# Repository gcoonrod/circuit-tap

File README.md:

<!--
 Copyright 2023 Greg Coonrod
 
 Licensed under the Apache License, Version 2.0 (the "License");
 you may not use this file except in compliance with the License.
 You may obtain a copy of the License at
 
     http://www.apache.org/licenses/LICENSE-2.0
 
 Unless required by applicable law or agreed to in writing, software
 distributed under the License is distributed on an "AS IS" BASIS,
 WITHOUT WARRANTIES OR CONDITIONS OF ANY KIND, either express or implied.
 See the License for the specific language governing permissions and
 limitations under the License.
-->

# Circuit Tap

A low-speed digital logic analyzer designed around 74HC165 shift registers and the ATMega4809 MCU.

## Design

The Circuit Tap is designed to serve as a digital logic analyzer for primarily low speed circuits (<= 1Mhz). It is intended to aid in debugging the [RetroStack](https://github.com/gcoonrod/retro-stack), a 6502 based hobbyist computer. As I do not (at the time of designing this tool) own an oscilliscope or logic analyzer, I needed a way to monitor the address bus, data bus, and numerous control signals of the RetroStack while the clock was freely running. For very simple programs it was sufficient to use a manually stepped clock to debug, but the addition of IO peripherals and more complex programs have made it prohibitively time consuming to continue manual clock control.

### Data Capture

The Circuit Tap has 6 low speed 8-bit input ports and one full speed 8-bit port. The low speed ports are implemented with 74HC165 parallel load shift registers which allows for the simultaneous capture of up to 48 signals on a single clock transition. However, those bits must be shifted out before (~10 mcu clock cycles) before another sample can be taken. This is the primary limiting factor for the sampling speed of the low speed inputs. The full speed port is directly mapped to Port D of the 4809 and can be read from or written to as fast as the mcu is capable.

### Goals

- Reliably capture signals at ~1Mhz
- Read test plans from an SD card or UART
- Write test results to SD or UART
- Integrate with desktop GUI (TBD)
- Drive external clock and control lines
- Trigger off external clock and control lines

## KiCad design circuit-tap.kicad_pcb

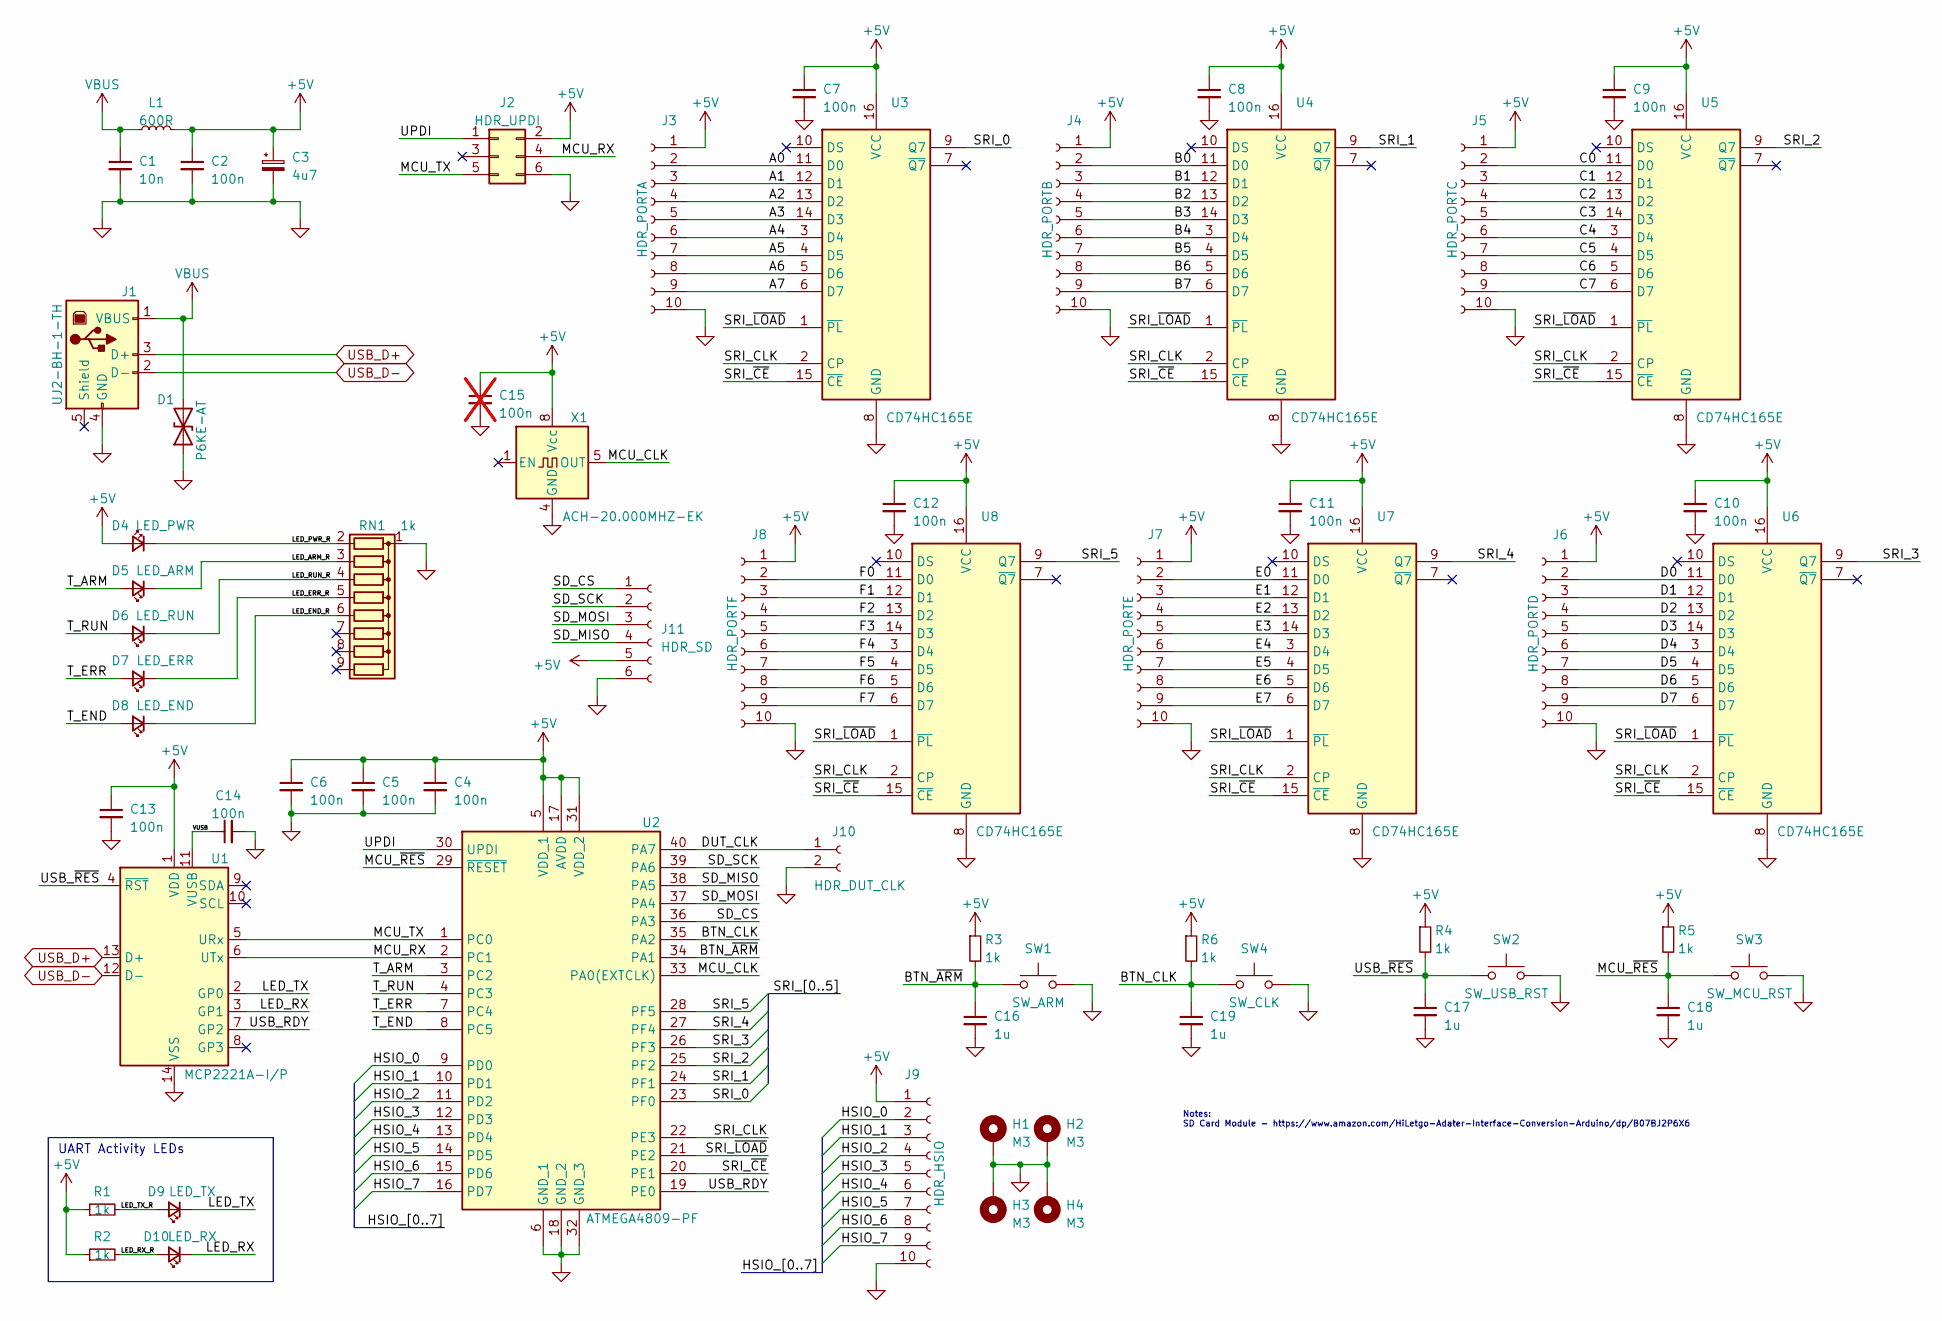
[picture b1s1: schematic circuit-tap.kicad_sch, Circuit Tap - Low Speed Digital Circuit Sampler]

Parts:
C1: 10n; C_Rect_L4.0mm_W2.5mm_P2.50mm; Manufacturer Part K103K10X7RF53L2
C2, C4, C5, C6, C7, C8, C9, C10, C11, C12, C13, C14: 100n; C_Rect_L4.0mm_W2.5mm_P2.50mm; Manufacturer Part K104K15X7RF5TL2
C3: 4u7; CP_Radial_D5.0mm_P2.50mm; Manufacturer Part ECE-A1VKS4R7I
C15: 100n; C_Rect_L4.0mm_W2.5mm_P2.50mm; Manufacturer Part K104K15X7RF5TL2; not fitted
C16, C17, C18, C19: 1u; C_Rect_L4.6mm_W3.8mm_P2.50mm_MKS02_FKP02; Manufacturer Part FG18X7R1E105KRT00
D1: P6KE-AT; D_DO-15_P3.81mm_Vertical_AnodeUp; Manufacturer Part P6KE6.8CA-AT/B
D4: LED_PWR; LED_D5.0mm; Manufacturer Part WP7113ID
D5: LED_ARM; LED_D5.0mm; Manufacturer Part WP7113YT
D6: LED_RUN; LED_D5.0mm; Manufacturer Part WP7113GD
D7: LED_ERR; LED_D5.0mm; Manufacturer Part WP7113ID
D8: LED_END; LED_D5.0mm; Manufacturer Part WP7113GD
D9: LED_TX; LED_D5.0mm; Manufacturer Part WP7113YT
D10: LED_RX; LED_D5.0mm; Manufacturer Part WP7113YT
H1, H2, H3, H4: M3; MountingHole_3.2mm_M3_DIN965_Pad
J1: UJ2-BH-1-TH; UJ2BH1TH; Manufacturer Part UJ2-BH-1-TH
J2: HDR_UPDI; PinHeader_2x03_P2.54mm_Vertical; Manufacturer Part 10129381-906002BLF
J3: HDR_PORTA; PinSocket_1x10_P2.54mm_Vertical; Manufacturer Part 61301011821
J4: HDR_PORTB; PinSocket_1x10_P2.54mm_Vertical; Manufacturer Part 61301011821
J5: HDR_PORTC; PinSocket_1x10_P2.54mm_Vertical; Manufacturer Part 61301011821
J6: HDR_PORTD; PinSocket_1x10_P2.54mm_Vertical; Manufacturer Part 61301011821
J7: HDR_PORTE; PinSocket_1x10_P2.54mm_Vertical; Manufacturer Part 61301011821
J8: HDR_PORTF; PinSocket_1x10_P2.54mm_Vertical; Manufacturer Part 61301011821
J9: HDR_HSIO; PinSocket_1x10_P2.54mm_Vertical; Manufacturer Part 61301011821
J10: HDR_DUT_CLK; PinSocket_1x02_P2.54mm_Vertical; Manufacturer Part 801-87-002-10-001101
J11: HDR_SD; PinSocket_1x06_P2.54mm_Vertical; Manufacturer Part 61300611821
L1: 600R; LairdTech_28C0236-0JW-10; Manufacturer Part 28C0236-0JW-10
R1, R2, R3, R4, R5, R6: 1k; R_Axial_DIN0204_L3.6mm_D1.6mm_P5.08mm_Horizontal; Manufacturer Part MBA02040C1001FCT00
RN1: 1k; R_Array_SIP9; Manufacturer Part 4609X-101-102LF
SW1: SW_ARM; SW_PUSH_6mm; Manufacturer Part TS02-66-70-BK-260-LCR-D
SW2: SW_USB_RST; SW_PUSH_6mm; Manufacturer Part FSM4JAH
SW3: SW_MCU_RST; SW_PUSH_6mm; Manufacturer Part FSM4JAH
SW4: SW_CLK; SW_PUSH_6mm; Manufacturer Part TS02-66-70-BK-260-LCR-D
U1: MCP2221A-I/P; DIP-14_W7.62mm; Manufacturer Part MCP2221A-I/P
U2: ATMEGA4809-PF; DIP-40_W15.24mm_Socket_LongPads; Manufacturer Part ATMEGA4809-PF
U3, U4, U5, U6, U7, U8: CD74HC165E; DIP-16_W7.62mm_Socket_LongPads; Manufacturer Part CD74HC165E
X1: ACH-20.000MHZ-EK; Oscillator_DIP-8; Manufacturer Part ACH-20.000MHZ-EK

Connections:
+5V: C2.1, C3.1, C4.1, C5.1, C6.1, C7.1, C8.1, C9.1, C10.1, C11.1, C12.1, C13.1, C15.1, D4.2 (A), J2.2, J3.1, J4.1, J5.1, J6.1, J7.1, J8.1, J9.1, J11.5, L1.2, R1.1, R2.1, R3.1, R4.1, R5.1, R6.1, U1.1 (VDD), U2.5 (VDD_1), U2.17 (AVDD), U2.31 (VDD_2), U3.16 (VCC), U4.16 (VCC), U5.16 (VCC), U6.16 (VCC), U7.16 (VCC), U8.16 (VCC), X1.8 (Vcc)
/A0: J3.2, U3.11 (D0)
/A1: J3.3, U3.12 (D1)
/A2: J3.4, U3.13 (D2)
/A3: J3.5, U3.14 (D3)
/A4: J3.6, U3.3 (D4)
/A5: J3.7, U3.4 (D5)
/A6: J3.8, U3.5 (D6)
/A7: J3.9, U3.6 (D7)
/B0: J4.2, U4.11 (D0)
/B1: J4.3, U4.12 (D1)
/B2: J4.4, U4.13 (D2)
/B3: J4.5, U4.14 (D3)
/B4: J4.6, U4.3 (D4)
/B5: J4.7, U4.4 (D5)
/B6: J4.8, U4.5 (D6)
/B7: J4.9, U4.6 (D7)
/BTN_CLK: C19.1, R6.2, SW4.1, U2.35 (PA2)
/BTN_~ARM: C16.1, R3.2, SW1.1, U2.34 (PA1)
/C0: J5.2, U5.11 (D0)
/C1: J5.3, U5.12 (D1)
/C2: J5.4, U5.13 (D2)
/C3: J5.5, U5.14 (D3)
/C4: J5.6, U5.3 (D4)
/C5: J5.7, U5.4 (D5)
/C6: J5.8, U5.5 (D6)
/C7: J5.9, U5.6 (D7)
/D0: J6.2, U6.11 (D0)
/D1: J6.3, U6.12 (D1)
/D2: J6.4, U6.13 (D2)
/D3: J6.5, U6.14 (D3)
/D4: J6.6, U6.3 (D4)
/D5: J6.7, U6.4 (D5)
/D6: J6.8, U6.5 (D6)
/D7: J6.9, U6.6 (D7)
/DUT_CLK: J10.1, U2.40 (PA7)
/E0: J7.2, U7.11 (D0)
/E1: J7.3, U7.12 (D1)
/E2: J7.4, U7.13 (D2)
/E3: J7.5, U7.14 (D3)
/E4: J7.6, U7.3 (D4)
/E5: J7.7, U7.4 (D5)
/E6: J7.8, U7.5 (D6)
/E7: J7.9, U7.6 (D7)
/F0: J8.2, U8.11 (D0)
/F1: J8.3, U8.12 (D1)
/F2: J8.4, U8.13 (D2)
/F3: J8.5, U8.14 (D3)
/F4: J8.6, U8.3 (D4)
/F5: J8.7, U8.4 (D5)
/F6: J8.8, U8.5 (D6)
/F7: J8.9, U8.6 (D7)
/HSIO_0: J9.2, U2.9 (PD0)
/HSIO_1: J9.3, U2.10 (PD1)
/HSIO_2: J9.4, U2.11 (PD2)
/HSIO_3: J9.5, U2.12 (PD3)
/HSIO_4: J9.6, U2.13 (PD4)
/HSIO_5: J9.7, U2.14 (PD5)
/HSIO_6: J9.8, U2.15 (PD6)
/HSIO_7: J9.9, U2.16 (PD7)
/LED_ARM_R: D5.1 (K), RN1.3 (R2)
/LED_END_R: D8.1 (K), RN1.6 (R5)
/LED_ERR_R: D7.1 (K), RN1.5 (R4)
/LED_PWR_R: D4.1 (K), RN1.2 (R1)
/LED_RUN_R: D6.1 (K), RN1.4 (R3)
/LED_RX: D10.1 (K), U1.3 (GP1)
/LED_RX_R: D10.2 (A), R2.2
/LED_TX: D9.1 (K), U1.2 (GP0)
/LED_TX_R: D9.2 (A), R1.2
/MCU_CLK: U2.33 (PA0(EXTCLK)), X1.5 (OUT)
/MCU_RX: J2.4, U1.6 (UTx), U2.2 (PC1)
/MCU_TX: J2.5, U1.5 (URx), U2.1 (PC0)
/MCU_~RES: C18.1, R5.2, SW3.1, U2.29 (~RESET)
/SD_CS: J11.1, U2.36 (PA3)
/SD_MISO: J11.4, U2.38 (PA5)
/SD_MOSI: J11.3, U2.37 (PA4)
/SD_SCK: J11.2, U2.39 (PA6)
/SRI_0: U2.23 (PF0), U3.9 (Q7)
/SRI_1: U2.24 (PF1), U4.9 (Q7)
/SRI_2: U2.25 (PF2), U5.9 (Q7)
/SRI_3: U2.26 (PF3), U6.9 (Q7)
/SRI_4: U2.27 (PF4), U7.9 (Q7)
/SRI_5: U2.28 (PF5), U8.9 (Q7)
/SRI_CLK: U2.22 (PE3), U3.2 (CP), U4.2 (CP), U5.2 (CP), U6.2 (CP), U7.2 (CP), U8.2 (CP)
/SRI_~CE: U2.20 (PE1), U3.15 (~CE), U4.15 (~CE), U5.15 (~CE), U6.15 (~CE), U7.15 (~CE), U8.15 (~CE)
/SRI_~LOAD: U2.21 (PE2), U3.1 (~PL), U4.1 (~PL), U5.1 (~PL), U6.1 (~PL), U7.1 (~PL), U8.1 (~PL)
/T_ARM: D5.2 (A), U2.3 (PC2)
/T_END: D8.2 (A), U2.8 (PC5)
/T_ERR: D7.2 (A), U2.7 (PC4)
/T_RUN: D6.2 (A), U2.4 (PC3)
/UPDI: J2.1, U2.30 (UPDI)
/USB_RDY: U1.7 (GP2), U2.19 (PE0)
/USB_~RES: C17.1, R4.2, SW2.1, U1.4 (~RST)
/VUSB: C14.1, U1.11 (VUSB)
GND: C1.2, C2.2, C3.2, C4.2, C5.2, C6.2, C7.2, C8.2, C9.2, C10.2, C11.2, C12.2, C13.2, C14.2, C15.2, C16.2, C17.2, C18.2, C19.2, D1.1 (A1), H1.1, H2.1, H3.1, H4.1, J1.4 (GND), J2.6, J3.10, J4.10, J5.10, J6.10, J7.10, J8.10, J9.10, J10.2, J11.6, RN1.1 (common), SW1.2, SW2.2, SW3.2, SW4.2, U1.14 (VSS), U2.6 (GND_1), U2.18 (GND_2), U2.32 (GND_3), U3.8 (GND), U4.8 (GND), U5.8 (GND), U6.8 (GND), U7.8 (GND), U8.8 (GND), X1.4 (GND)
USB_D+: J1.3 (D+), U1.13 (D+)
USB_D-: J1.2 (D-), U1.12 (D-)
VBUS: C1.1, D1.2 (A2), J1.1 (VBUS), L1.1

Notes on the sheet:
Notes: SD Card Module - https://www.amazon.com/HiLetgo-Adater-Interface-Conversion-Arduino/dp/B07BJ2P6X6
UART Activity LEDs

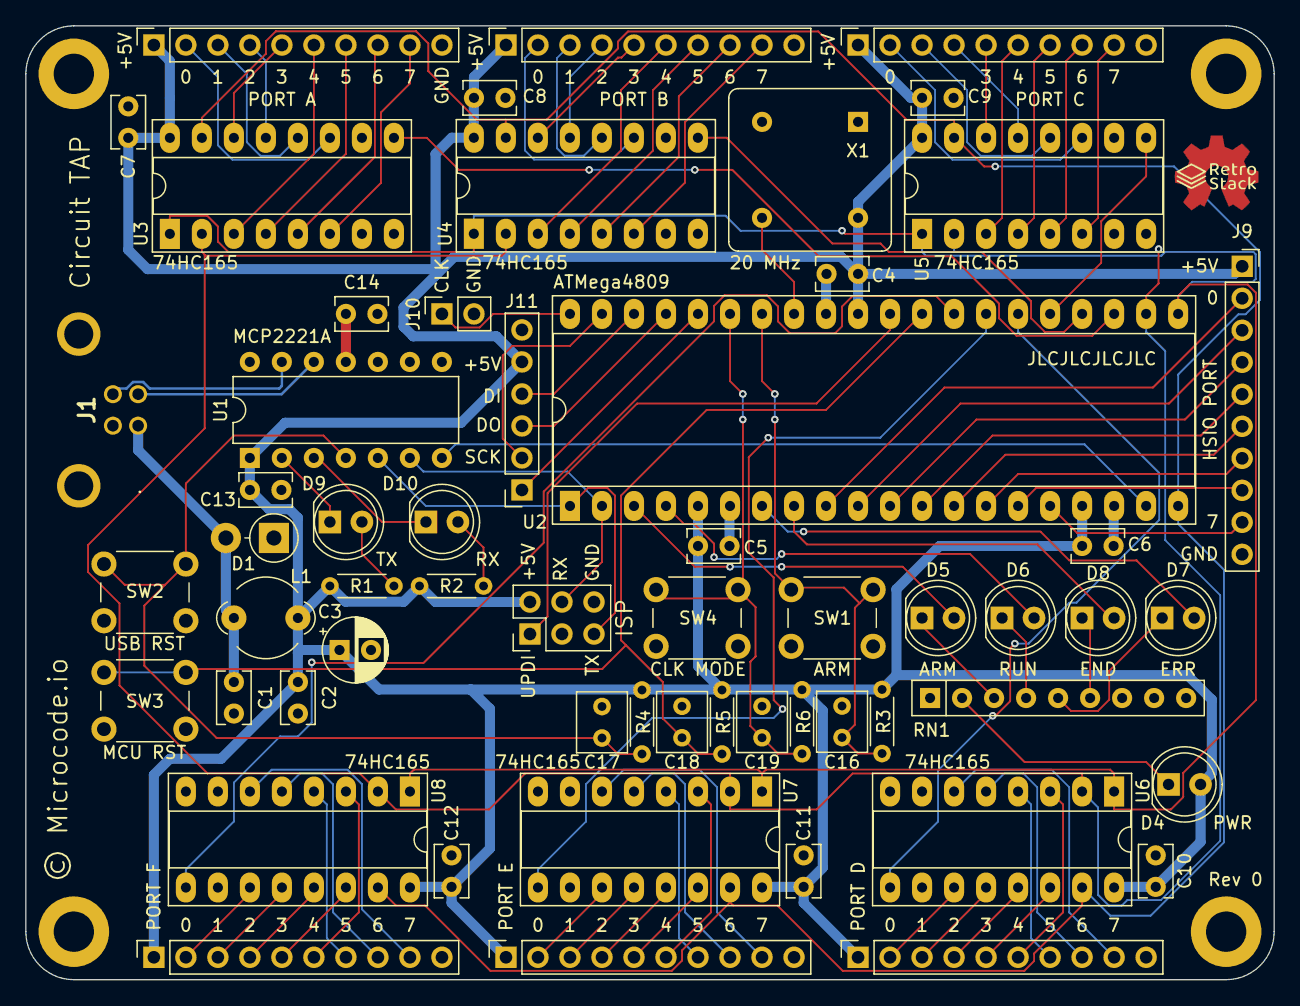
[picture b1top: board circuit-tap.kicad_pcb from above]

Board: 4 copper layers, 99.1 x 75.7 mm, 62 parts (0 on the bottom side), 98 nets.

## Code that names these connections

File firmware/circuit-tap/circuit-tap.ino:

// Copyright 2023 Greg Coonrod
//
// Licensed under the Apache License, Version 2.0 (the "License");
// you may not use this file except in compliance with the License.
// You may obtain a copy of the License at
//
//     http://www.apache.org/licenses/LICENSE-2.0
//
// Unless required by applicable law or agreed to in writing, software
// distributed under the License is distributed on an "AS IS" BASIS,
// WITHOUT WARRANTIES OR CONDITIONS OF ANY KIND, either express or implied.
// See the License for the specific language governing permissions and
// limitations under the License.

#define F_CPU 20000000UL
#define __DEBUG__

// Library and System Includes
#include <Arduino.h>
#include <avr/io.h>
#include <SPI.h>
#include <SD.h>

// Local Includes
#include "src/CircuitTap.h"

// Circuit Tap

// Define pins on the ATMega4809 40-pin DIP package
// UART 1 default pins
#define MCU_TX PIN_PC0
#define MCU_RX PIN_PC1

// State LEDs
#define T_ARM PIN_PC2
#define T_RUN PIN_PC3
#define T_ERR PIN_PC4
#define T_END PIN_PC5

// High Speed IO (HSIO) uses Port D [0..7]
// Use the native AVR port registers for speed
#define HSIO_PORT PORTD
#define HSIO_DDR PORTD.DIR
#define HSIO_PIN PORTD.PIN
#define HSIO_MASK 0b00000000

// SPI Pins and Selects
// Primarily intended for SD card use
#define SPI_MOSI PIN_SPI_MOSI
#define SPI_MISO PIN_SPI_MISO
#define SPI_SCK PIN_SPI_SCK
#define SPI_CS PIN_PA3

// Buttons
// All active low
#define BTN_MODE PIN_PA2
#define BTN_ARM PIN_PA1

// Device Under Test (DUT) Clock IO
#define DUT_CLK PIN_PA7

// MCP2221A USB Ready Signal
#define USB_RDY PIN_PE0

// Global Variables/State


// Global FSM
static StateManager manager;
SRPortManager srPort;

// LEDs Setup
void setup_leds()
{
    pinMode(T_ARM, OUTPUT);
    pinMode(T_RUN, OUTPUT);
    pinMode(T_ERR, OUTPUT);
    pinMode(T_END, OUTPUT);
}

// Buttons Setup
void setup_btns()
{
    pinMode(BTN_ARM, INPUT);
    pinMode(BTN_MODE, INPUT);
}

// HSIO Port Setup
void setup_hsio_port(uint8_t bitmask)
{
    HSIO_DDR = bitmask;
}

// SPI Setup
void setup_spi()
{
    pinMode(SPI_MOSI, OUTPUT);
    pinMode(SPI_MISO, INPUT);
    pinMode(SPI_SCK, OUTPUT);
    pinMode(SPI_CS, OUTPUT);

    // Disable CS by default
    digitalWrite(SPI_CS, HIGH);
}

// USB Ready Setup
void setup_usb_rdy()
{
    pinMode(USB_RDY, INPUT);
}

// DUT Clock Setup
void setup_dut_clk()
{
    pinMode(DUT_CLK, INPUT);
}

// Setup SD Card
void setup_sd()
{
    // Setup SPI
    setup_spi();

    // Setup SD Card
    if (!SD.begin(SPI_CS))
    {
        Serial1.println("SD Card failed to initialize");
        manager.setErrorState(true);
    }
    Serial1.println("SD Card initialized");
}

// Button ISRs
void btn_arm_isr()
{
    Serial1.println("ARM Button Pressed");
    if (manager.getArmState() == FSM::ArmState::Disarmed)
    {
        // If Disarmed and Running, End
        if (manager.getRunState() == FSM::RunState::Running)
        {
            manager.setRunState(FSM::RunState::Ended);
        }
        else if (manager.getRunState() == FSM::RunState::Ended)
        {
            manager.setRunState(FSM::RunState::Stopped);
        }
        else
        {
            manager.setArmState(FSM::ArmState::Armed);
        }
    }
    else
    {
        manager.setArmState(FSM::ArmState::Disarmed);
    }
}

void btn_mode_isr()
{
    Serial1.println("MODE Button Pressed");
    manager.cycleClkModeState();
}

// DUT Clock ISR
void dut_clk_isr()
{

    // If armed, start running and disarm
    if (manager.getArmState() == FSM::ArmState::Armed)
    {
        Serial1.println(F("Run started by DUT Clock Interrupt"));
        manager.setRunState(FSM::RunState::Running);
        manager.setArmState(FSM::ArmState::Disarmed);
    }

    // If running, trigger SR latch and shift in data
    if (manager.getRunState() == FSM::RunState::Running)
    {
        Serial1.println(F("Placeholder for SR Latch Trigger"));
        // TODO Trigger SR Latch and Shift in Data
        // TODO if ISR is triggered before Shift in is complete set Error state and end run
    }

    // If ended or stopped do nothing
    if (manager.getRunState() == FSM::RunState::Ended || manager.getRunState() == FSM::RunState::Stopped)
    {
#ifdef __DEBUG__
        Serial1.println(F("DUT Clock ISR while Stopped or Ended"));
#endif
        return;
    }
}

// LED Update
void updateLEDs(StateManager *manager)
{
    // Update ARM LED
    digitalWrite(T_ARM, manager->getArmState() == FSM::ArmState::Armed ? 1 : 0);

    // Update RUN and END LEDs
    switch (manager->getRunState())
    {
    case FSM::RunState::Running:
        digitalWrite(T_RUN, 1);
        digitalWrite(T_END, 0);
        break;
    case FSM::RunState::Stopped:
        digitalWrite(T_RUN, 0);
        digitalWrite(T_END, 0);
        break;
    case FSM::RunState::Ended:
        digitalWrite(T_RUN, 0);
        digitalWrite(T_END, 1);
        break;
    }

    // Update ERR LED
    digitalWrite(T_ERR, manager->getErrorState() ? 1 : 0);
}

// DUT Clock Update
void updateDUTClk(StateManager *manager)
{
    // Do nothing if RunState is Running
    if (manager->getRunState() == FSM::RunState::Running)
    {
        // A test is running, do not make any changes to
        return;
    }

    // Update DUT Clock
    switch (manager->getClkModeState())
    {
        // Output Mode, Disable DUT Clock Interrupt
    case FSM::ClkModeState::Output:
        detachInterrupt(DUT_CLK);
        pinMode(DUT_CLK, OUTPUT);
        break;
        // Input Mode, Enable DUT Clock Interrupt if Armed
    case FSM::ClkModeState::Input:
        if (manager->getArmState() == FSM::ArmState::Armed)
        {
            attachInterrupt(DUT_CLK, dut_clk_isr, FALLING);
        }
        else
        {
            detachInterrupt(DUT_CLK);
        }
        pinMode(DUT_CLK, INPUT_PULLUP);
        break;
        // HighZ Mode, Disable DUT Clock Interrupt
    case FSM::ClkModeState::HighZ:
        detachInterrupt(DUT_CLK);
        pinMode(DUT_CLK, INPUT);
        break;
    }
}

// Arduino Functions
void setup()
{

    // Setup State Manager
    manager = StateManager();

    // Setup SR Port Manager
    srPort = SRPortManager();
    srPort.begin();

    // Setup LEDs
    setup_leds();

    // Setup Buttons
    setup_btns();

    // Setup HSIO Port
    setup_hsio_port(HSIO_MASK);

    // Setup SPI
    setup_spi();

    // Setup USB Ready
    setup_usb_rdy();

    // Setup DUT Clock
    setup_dut_clk();

    // Attach ISRs
    attachInterrupt(BTN_ARM, btn_arm_isr, FALLING);
    attachInterrupt(BTN_MODE, btn_mode_isr, FALLING);

    Serial1.begin(115200);
    Serial1.println("Circuit Tap - Started");
}

void loop()
{
    // Update LEDs based on current state
    updateLEDs(&manager);

    // Update DUT clock based on current state
    updateDUTClk(&manager);

#ifdef __DEBUG__
    // Print Current State from State Manager to Serial
    if (manager.isDirty())
    {
        Serial1.println(manager);
    }
#endif

    // Update State Manager
    manager.update();
}

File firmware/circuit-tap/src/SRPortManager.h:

// Copyright 2023 Greg Coonrod
//
// Licensed under the Apache License, Version 2.0 (the "License");
// you may not use this file except in compliance with the License.
// You may obtain a copy of the License at
//
//     http://www.apache.org/licenses/LICENSE-2.0
//
// Unless required by applicable law or agreed to in writing, software
// distributed under the License is distributed on an "AS IS" BASIS,
// WITHOUT WARRANTIES OR CONDITIONS OF ANY KIND, either express or implied.
// See the License for the specific language governing permissions and
// limitations under the License.

#ifndef SRPORTMANAGER_H
#define SRPORTMANAGER_H

#include <Arduino.h>
#include <avr/io.h>

#define SRI_PORT_COUNT 6

// Shift Register Inputs (SRI) Control Pins
#define SRI_CTRL_PORT PORTE
#define SRI_CEB_PIN PIN_PE1   // Active Low
#define SRI_LOADB_PIN PIN_PE2 // Active Low
#define SRI_CLK_PIN PIN_PE3

#define SRI_CEB_bm PIN1_bm
#define SRI_LOADB_bm PIN2_bm
#define SRI_CLK_bm PIN3_bm

// Shift Register Inputs (SRI) Data Pins Port F [0..5]
// Uses the native AVR port registers for speed
// PF6 reserved for RESETB
// All pins are input only
#define SRI_DATA_PORT PORTF
#define SRI_DATA_DDR PORTF.DIR
#define SRI_DATA_PIN PORTF.PIN
#define SRI_DATA_MASK 0b0000000

#define SRI_PORTA_bm PIN0_bm
#define SRI_PORTB_bm PIN1_bm
#define SRI_PORTC_bm PIN2_bm
#define SRI_PORTD_bm PIN3_bm
#define SRI_PORTE_bm PIN4_bm
#define SRI_PORTF_bm PIN5_bm

/**
 * Shift Register Port Manager Class
 * The SRPortManager is intended to manage the interactions with the shift registers
 * that make up the low-speed input ports A through F of the Circuit Tap. The six shift
 * registers (74HC165) are joined in parallel to form a 48-bit shift register. The control
 * lines for the shift registers are connected to Port E (PE1-PE3) of the ATMega4809. The
 * serial data out (QH) of each shift register is connected to Port F (PF0-PF5) of the
 * ATMega4809.
 */
class SRPortManager
{
public:
    // Constructor
    SRPortManager();

    void begin();

    void shiftInAllPorts();
    
    uint8_t shiftInPort(uint8_t port);

    static uint8_t getByte(uint8_t index);

private:
    static uint8_t _shiftData[SRI_PORT_COUNT];
};

#endif

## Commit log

2023-06-15 Board rev 0
2023-06-18 Docs updates and WIP firmware.
2023-06-23 Wip before switching to platformio

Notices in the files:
circuit-tap.kicad_pcb:
© Microcode.io
